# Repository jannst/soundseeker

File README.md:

# Soundseeker
The Soundseeker project originated from my need to measure the speed of sound traveling through wood, a crucial characteristic in selecting wood for musical instrument making. Regrettably, there was no affordable method available, prompting me to embark on building a device capable of measuring this parameter independently. The project commenced in 2017 with the development of the initial prototype. Throughout the process, I gained valuable insights, and I am currently at the third prototype stage, incorporating a custom PCB, surface-mount device (SMD) parts and even a step-up DC-DC converter to drive the piezo acuator.

This Repository contains only the source code for the third prototype.

## Prototype I (2017)
<div style="display: flex">

</div>
The first prototype used an ATMEAGA-8 as MCU and a Haribo sweets box as enclosure. 

## Prototype II (2020)

The second prototype uses a very powerful Teensy 4 board and utilises a display which even allows to visualise the waveform.

## Prototype III (2022)

The third prototype features custom PCBs and utilizes the RP2040 microcontroller, providing USB connectivity. The display was omitted to enable visualization of transmitted data through laptops or mobile phones connected via USB. The pre-amplifier for the piezo sensor is situated on the PCB to which the sensor is soldered, ensuring a very short, high-impedance signal path.

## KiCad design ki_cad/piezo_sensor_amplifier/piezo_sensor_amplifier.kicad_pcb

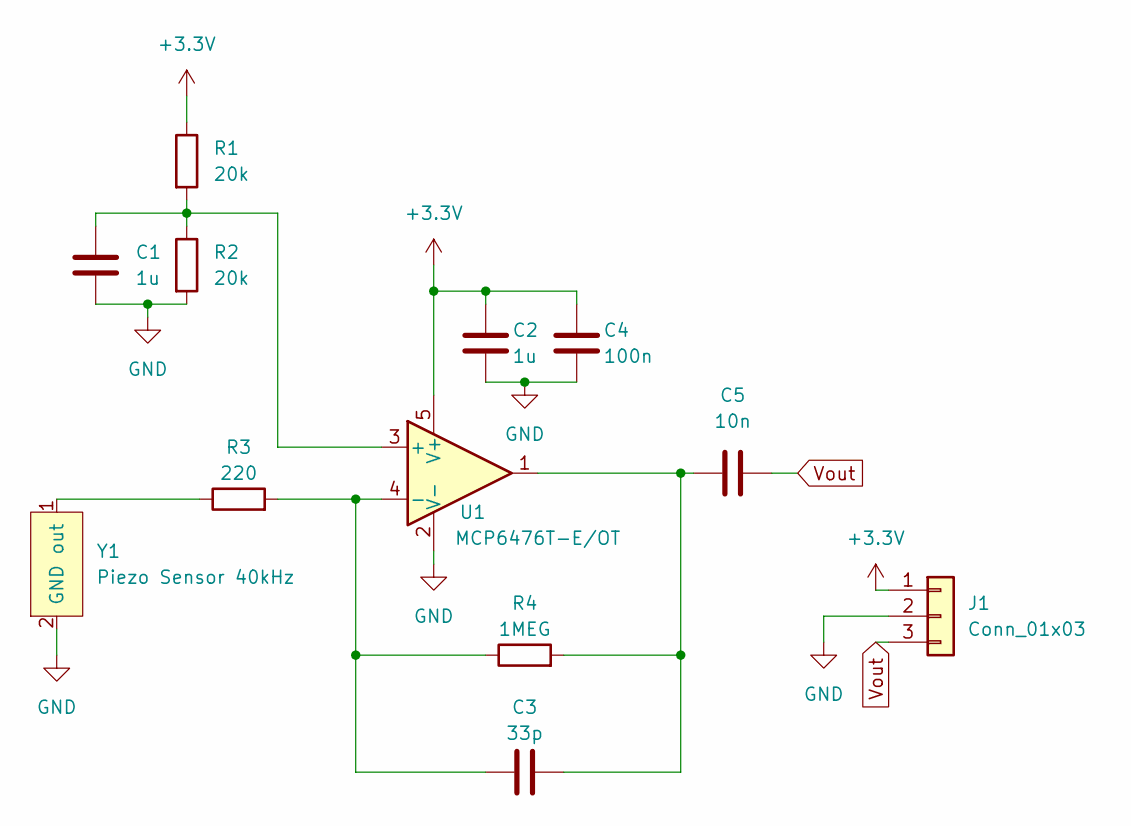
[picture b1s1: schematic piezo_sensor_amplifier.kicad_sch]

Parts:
C1, C2: 1u; R_0805_2012Metric_Pad1.20x1.40mm_HandSolder
C3: 33p; C_0805_2012Metric_Pad1.18x1.45mm_HandSolder
C4: 100n; C_0805_2012Metric_Pad1.18x1.45mm_HandSolder
C5: 10n; C_0805_2012Metric_Pad1.18x1.45mm_HandSolder
J1: Conn_01x03; PinHeader_1x03_P2.54mm_Vertical
R1, R2: 20k; R_0805_2012Metric_Pad1.20x1.40mm_HandSolder
R3: 220; R_0805_2012Metric_Pad1.20x1.40mm_HandSolder
R4: 1MEG; R_0805_2012Metric_Pad1.20x1.40mm_HandSolder
U1: MCP6476T-E/OT; SOT-23-5
Y1: Piezo Sensor 40kHz; piezo_sensor_D25mm

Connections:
+3.3V: C2.1, C4.1, J1.1, R1.1, U1.5 (V+)
GND: C1.2, C2.2, C4.2, J1.2, R2.2, U1.2 (V-), Y1.2 (GND)
unnamed: C1.1, R1.2, R2.1, U1.3 (+)
unnamed: C3.1, R3.2, R4.1, U1.4 (-)
unnamed: C3.2, C5.1, R4.2, U1.1
unnamed: R3.1, Y1.1 (out)
Vout: C5.2, J1.3

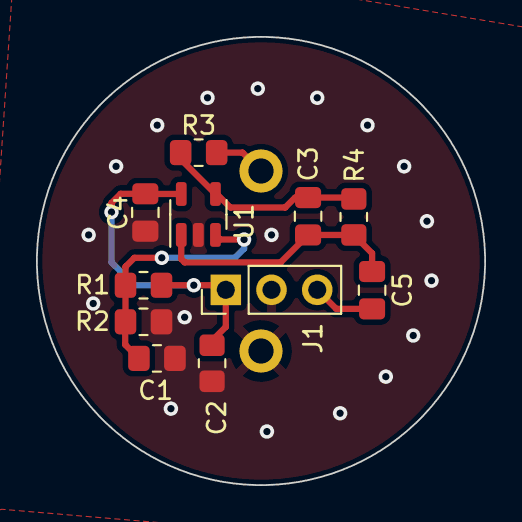
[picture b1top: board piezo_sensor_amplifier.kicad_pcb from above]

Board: 2 copper layers, 24.9 x 24.9 mm, 12 parts (0 on the bottom side), 7 nets.

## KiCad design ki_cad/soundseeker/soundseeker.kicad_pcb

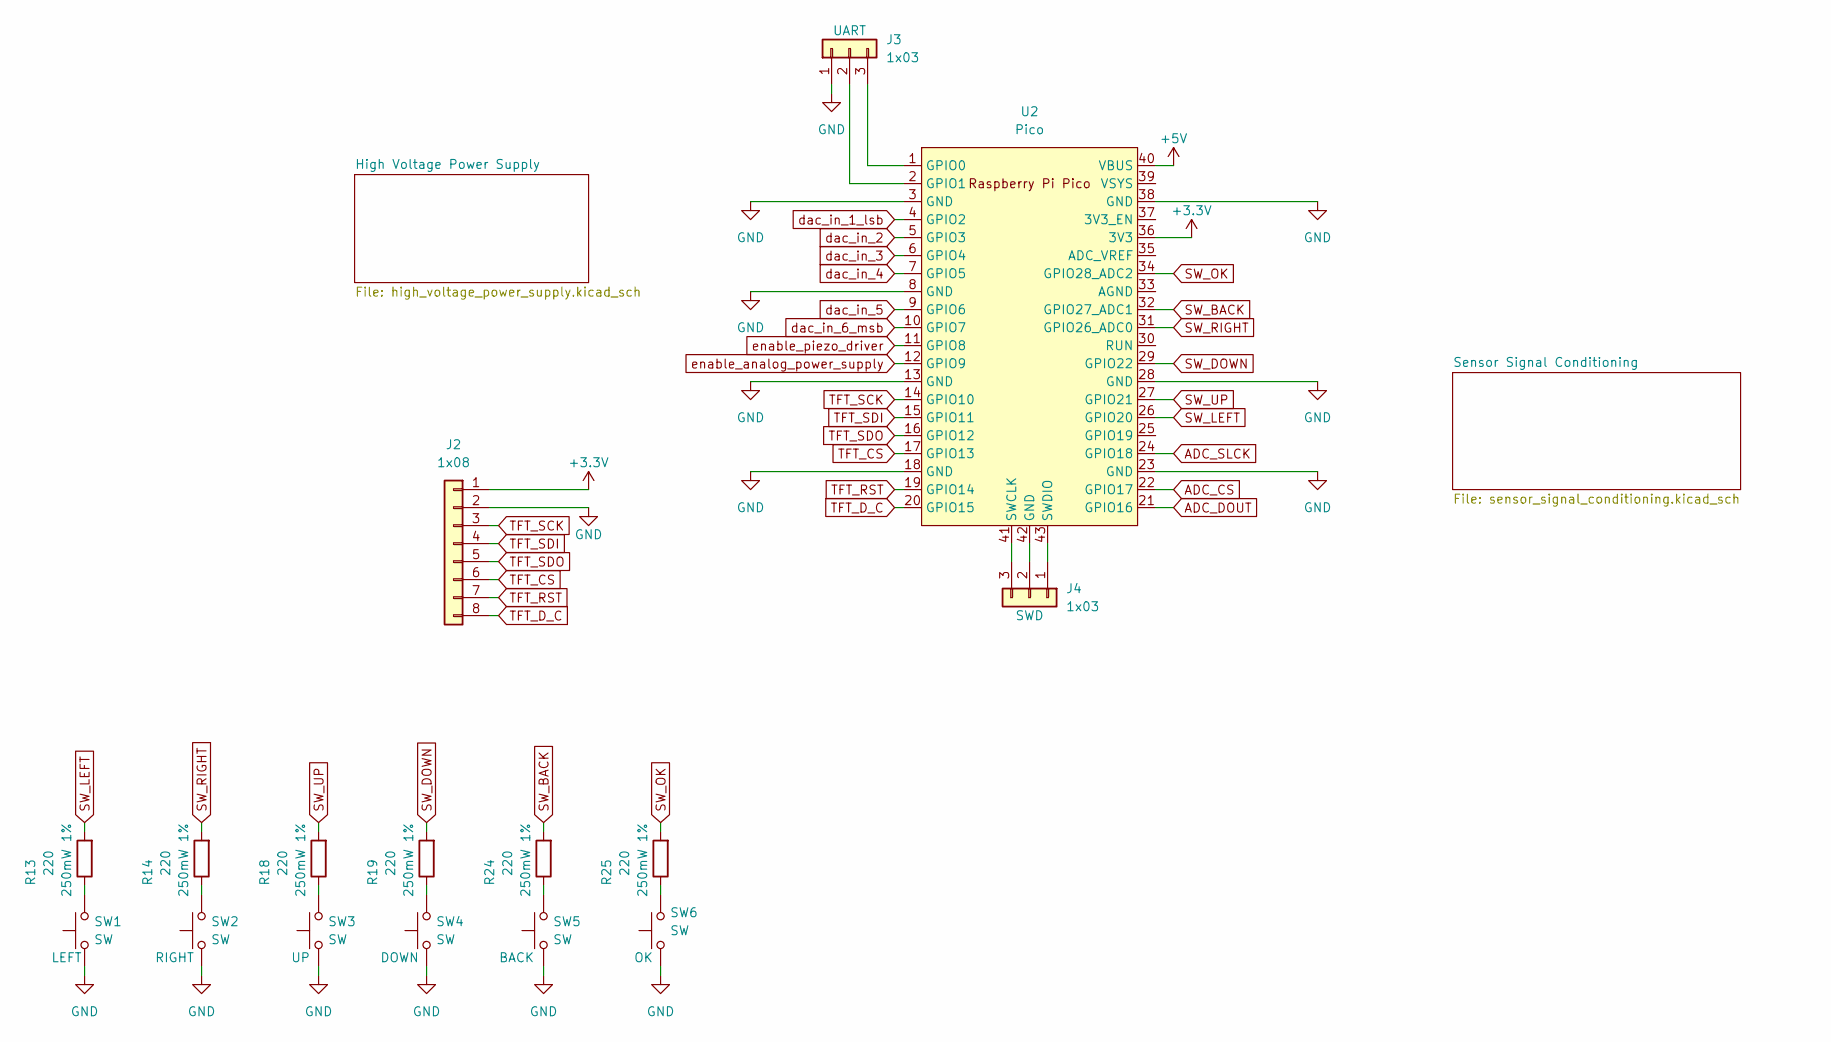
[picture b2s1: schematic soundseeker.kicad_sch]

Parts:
J2: 1x08; PinHeader_1x08_P2.54mm_Vertical
J3, J4: 1x03; PinHeader_1x03_P2.54mm_Vertical
R13, R14, R18, R19, R24, R25: 220; R_0805_2012Metric_Pad1.20x1.40mm_HandSolder
SW1, SW2, SW3, SW4, SW5, SW6: SW; SW_PUSH_6mm
U2: Pico; RPi_Pico_SMD_TH

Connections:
+3.3V: J2.1, U2.36 (3V3)
+5V: U2.40 (VBUS); also elsewhere on the board
ADC_CS: U2.22 (GPIO17); also elsewhere on the board
ADC_DOUT: U2.21 (GPIO16); also elsewhere on the board
ADC_SLCK: U2.24 (GPIO18); also elsewhere on the board
GND: J2.2, J3.1, SW1.1, SW2.1, SW3.1, SW4.1, SW5.1, SW6.1, U2.3 (GND), U2.8 (GND), U2.13 (GND), U2.18 (GND), U2.23 (GND), U2.28 (GND), U2.38 (GND); also elsewhere on the board
unnamed: J3.2, U2.2 (GPIO1)
unnamed: J3.3, U2.1 (GPIO0)
unnamed: J4.1, U2.43 (SWDIO)
unnamed: J4.2, U2.42 (GND)
unnamed: J4.3, U2.41 (SWCLK)
unnamed: R13.1, SW1.2
unnamed: R14.1, SW2.2
unnamed: R18.1, SW3.2
unnamed: R19.1, SW4.2
unnamed: R24.1, SW5.2
unnamed: R25.1, SW6.2
SW_BACK: R24.2, U2.32 (GPIO27_ADC1)
SW_DOWN: R19.2, U2.29 (GPIO22)
SW_LEFT: R13.2, U2.26 (GPIO20)
SW_OK: R25.2, U2.34 (GPIO28_ADC2)
SW_RIGHT: R14.2, U2.31 (GPIO26_ADC0)
SW_UP: R18.2, U2.27 (GPIO21)
TFT_CS: J2.6, U2.17 (GPIO13)
TFT_D_C: J2.8, U2.20 (GPIO15)
TFT_RST: J2.7, U2.19 (GPIO14)
TFT_SCK: J2.3, U2.14 (GPIO10)
TFT_SDI: J2.4, U2.15 (GPIO11)
TFT_SDO: J2.5, U2.16 (GPIO12)
dac_in_1_lsb: U2.4 (GPIO2); also elsewhere on the board
dac_in_2: U2.5 (GPIO3); also elsewhere on the board
dac_in_3: U2.6 (GPIO4); also elsewhere on the board
dac_in_4: U2.7 (GPIO5); also elsewhere on the board
dac_in_5: U2.9 (GPIO6); also elsewhere on the board
dac_in_6_msb: U2.10 (GPIO7); also elsewhere on the board
enable_analog_power_supply: U2.12 (GPIO9); also elsewhere on the board
enable_piezo_driver: U2.11 (GPIO8); also elsewhere on the board

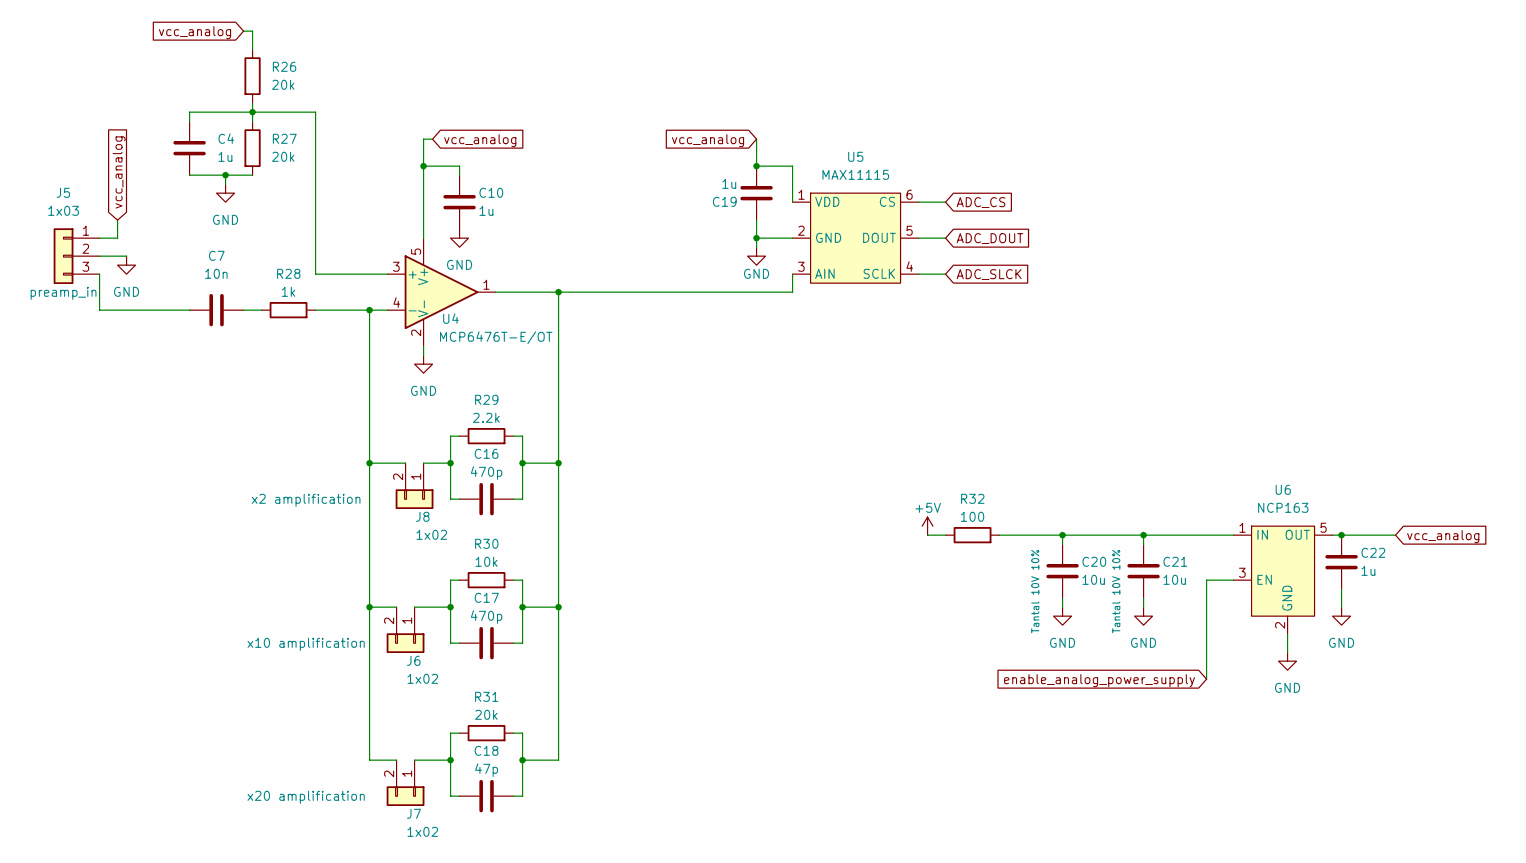
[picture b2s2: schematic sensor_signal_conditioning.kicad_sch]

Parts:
C4, C10, C19, C22: 1u; C_0805_2012Metric_Pad1.18x1.45mm_HandSolder
C7: 10n; C_0805_2012Metric_Pad1.18x1.45mm_HandSolder
C16, C17: 470p; C_0805_2012Metric_Pad1.18x1.45mm_HandSolder
C18: 47p; C_0805_2012Metric_Pad1.18x1.45mm_HandSolder
C20, C21: 10u; C_1206_3216Metric_Pad1.33x1.80mm_HandSolder
J5: 1x03; PinHeader_1x03_P2.54mm_Vertical
J6, J7, J8: 1x02; PinHeader_1x02_P2.54mm_Vertical
R26, R27, R31: 20k; R_0805_2012Metric_Pad1.20x1.40mm_HandSolder
R28: 1k; R_0805_2012Metric_Pad1.20x1.40mm_HandSolder
R29: 2.2k; R_0805_2012Metric_Pad1.20x1.40mm_HandSolder
R30: 10k; R_0805_2012Metric_Pad1.20x1.40mm_HandSolder
R32: 100; R_0805_2012Metric_Pad1.20x1.40mm_HandSolder
U4: MCP6476T-E/OT; SOT-23-5
U5: MAX11115; SOT-23-6_Handsoldering
U6: NCP163; SOT-23-5_HandSoldering

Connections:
+5V: R32.1; also elsewhere on the board
ADC_CS: U5.6 (CS); also elsewhere on the board
ADC_DOUT: U5.5 (DOUT); also elsewhere on the board
ADC_SLCK: U5.4 (SCLK); also elsewhere on the board
GND: C4.2, C10.2, C19.1, C20.2, C21.2, C22.2, J5.2, R27.2, U4.2 (V-), U5.2 (GND), U6.2 (GND); also elsewhere on the board
unnamed: C4.1, R26.2, R27.1, U4.3 (+)
unnamed: C7.1, J5.3
unnamed: C7.2, R28.1
unnamed: C16.1, J8.1, R29.1
unnamed: C16.2, C17.2, C18.2, R29.2, R30.2, R31.2, U4.1, U5.3 (AIN)
unnamed: C17.1, J6.1, R30.1
unnamed: C18.1, J7.1, R31.1
unnamed: C20.1, C21.1, R32.2, U6.1 (IN)
unnamed: J6.2, J7.2, J8.2, R28.2, U4.4 (-)
enable_analog_power_supply: U6.3 (EN); also elsewhere on the board
vcc_analog: C10.1, C19.2, C22.1, J5.1, R26.1, U4.5 (V+), U5.1 (VDD), U6.5 (OUT)

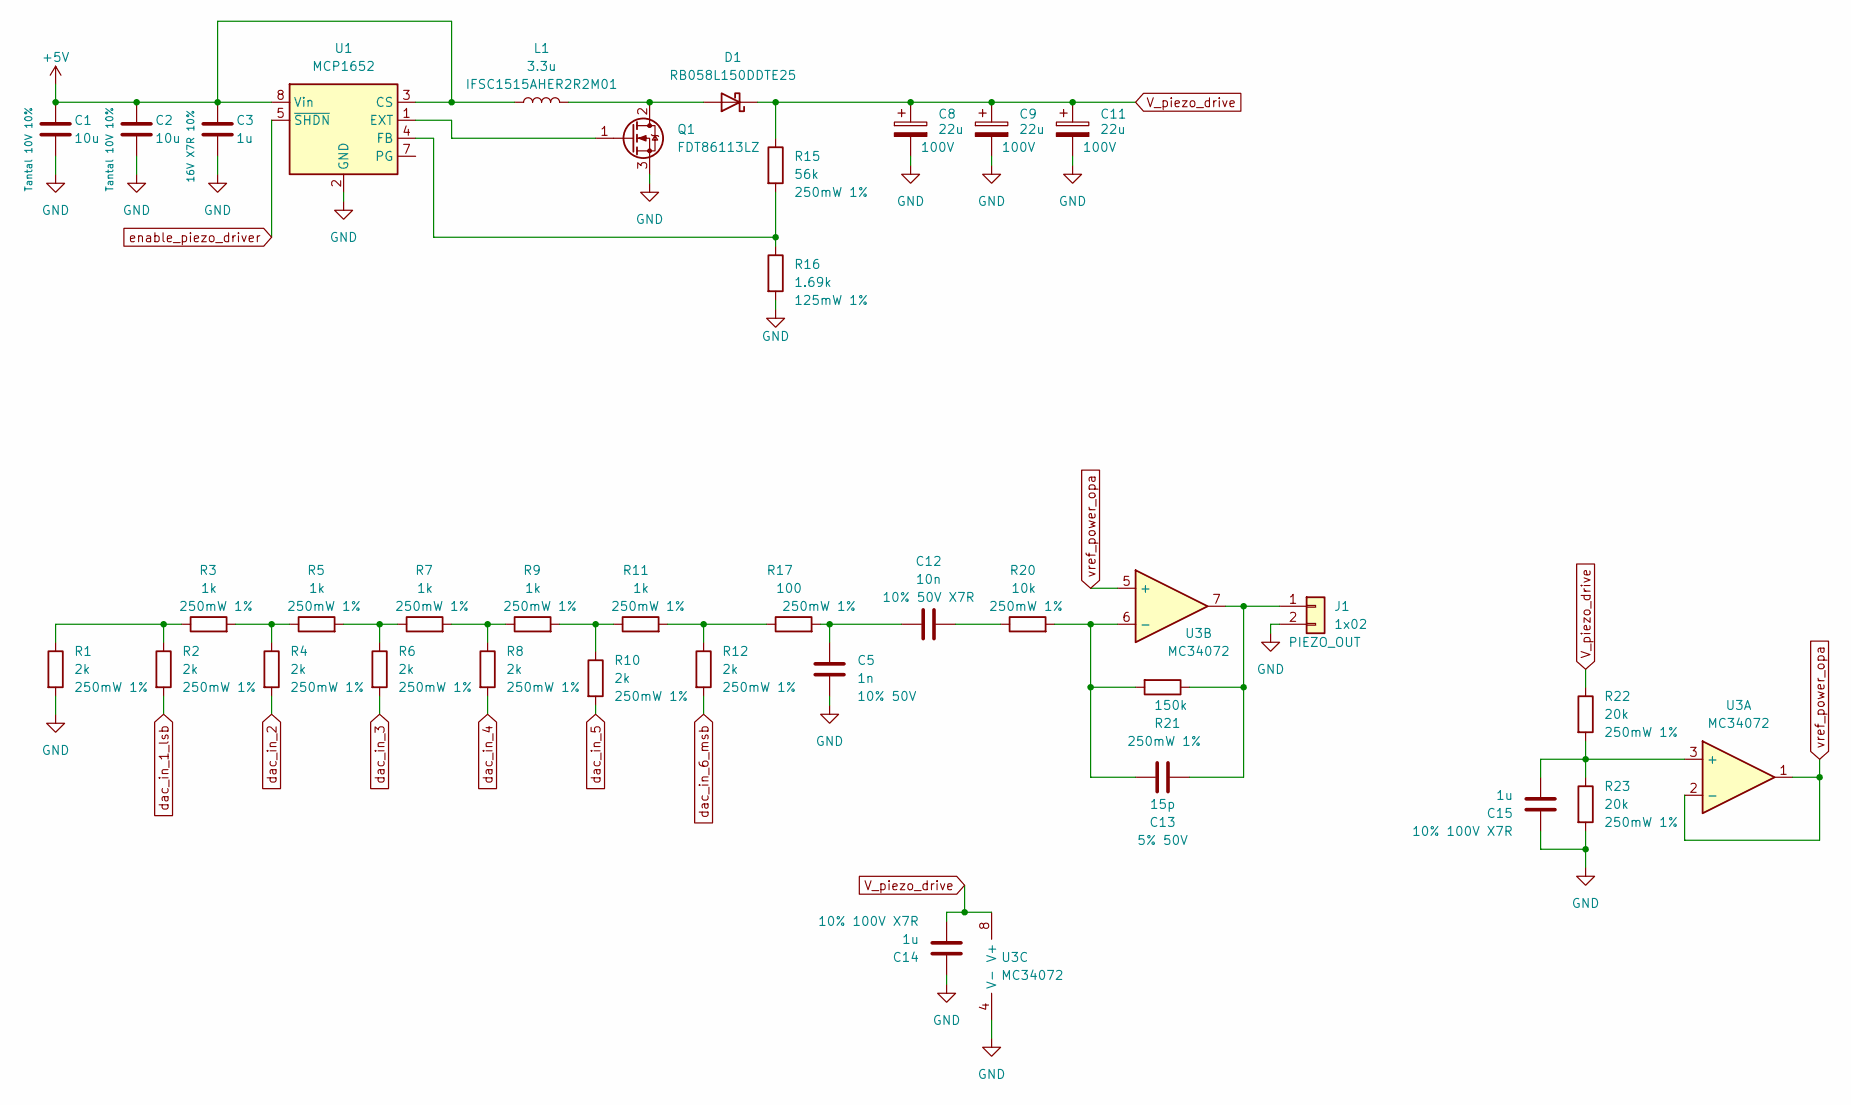
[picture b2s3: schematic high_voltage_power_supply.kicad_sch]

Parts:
C1, C2: 10u; C_1206_3216Metric_Pad1.33x1.80mm_HandSolder
C3: 1u; C_0805_2012Metric_Pad1.18x1.45mm_HandSolder
C5: 1n; C_0805_2012Metric_Pad1.18x1.45mm_HandSolder
C8, C9, C11: 22u; CP_Elec_8x10.5
C12: 10n; C_0805_2012Metric_Pad1.18x1.45mm_HandSolder
C13: 15p; C_0805_2012Metric_Pad1.18x1.45mm_HandSolder
C14, C15: 1u; C_1206_3216Metric_Pad1.33x1.80mm_HandSolder
D1: RB058L150DDTE25; D_SMA
J1: 1x02; PinHeader_1x02_P2.54mm_Vertical
L1: 3.3u; L_Vishay_IFSC-1515AH_4x4x1.8mm
Q1: FDT86113LZ; SOT-223-3_TabPin2
R1, R2, R4, R6, R8, R10, R12: 2k; R_0805_2012Metric_Pad1.20x1.40mm_HandSolder
R3, R5, R7, R9, R11: 1k; R_0805_2012Metric_Pad1.20x1.40mm_HandSolder
R15: 56k; R_0805_2012Metric_Pad1.20x1.40mm_HandSolder
R16: 1.69k; R_0805_2012Metric_Pad1.20x1.40mm_HandSolder
R17: 100; R_0805_2012Metric_Pad1.20x1.40mm_HandSolder
R20: 10k; R_0805_2012Metric_Pad1.20x1.40mm_HandSolder
R21: 150k; R_0805_2012Metric_Pad1.20x1.40mm_HandSolder
R22, R23: 20k; R_0805_2012Metric_Pad1.20x1.40mm_HandSolder
U1: MCP1652; MSOP-8_3x3mm_P0.65mm
U3: MC34072; SOIC-8_3.9x4.9mm_P1.27mm

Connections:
+5V: C1.1, C2.1, C3.1, L1.1, U1.3 (CS), U1.8 (Vin); also elsewhere on the board
GND: C1.2, C2.2, C3.2, C5.2, C8.2, C9.2, C11.2, C14.1, C15.1, J1.2, Q1.3 (S), R1.2, R16.2, R23.2, U1.2 (GND), U3.4 (V-); also elsewhere on the board
unnamed: C5.1, C12.1, R17.2
unnamed: C12.2, R20.1
unnamed: C13.1, J1.1, R21.1, U3.7
unnamed: C13.2, R20.2, R21.2, U3.6 (-)
unnamed: C15.2, R22.2, R23.1, U3.3 (+)
unnamed: D1.2 (A), L1.2, Q1.2 (D)
unnamed: Q1.1 (G), U1.1 (EXT)
unnamed: R1.1, R2.1, R3.1
unnamed: R3.2, R4.1, R5.1
unnamed: R5.2, R6.1, R7.1
unnamed: R7.2, R8.1, R9.1
unnamed: R9.2, R10.1, R11.1
unnamed: R11.2, R12.1, R17.1
unnamed: R15.2, R16.1, U1.4 (FB)
V_piezo_drive: C8.1, C9.1, C11.1, C14.2, D1.1 (K), R15.1, R22.1, U3.8 (V+)
dac_in_1_lsb: R2.2; also elsewhere on the board
dac_in_2: R4.2; also elsewhere on the board
dac_in_3: R6.2; also elsewhere on the board
dac_in_4: R8.2; also elsewhere on the board
dac_in_5: R10.2; also elsewhere on the board
dac_in_6_msb: R12.2; also elsewhere on the board
enable_piezo_driver: U1.5 (~SHDN); also elsewhere on the board
vref_power_opa: U3.1, U3.2 (-), U3.5 (+)

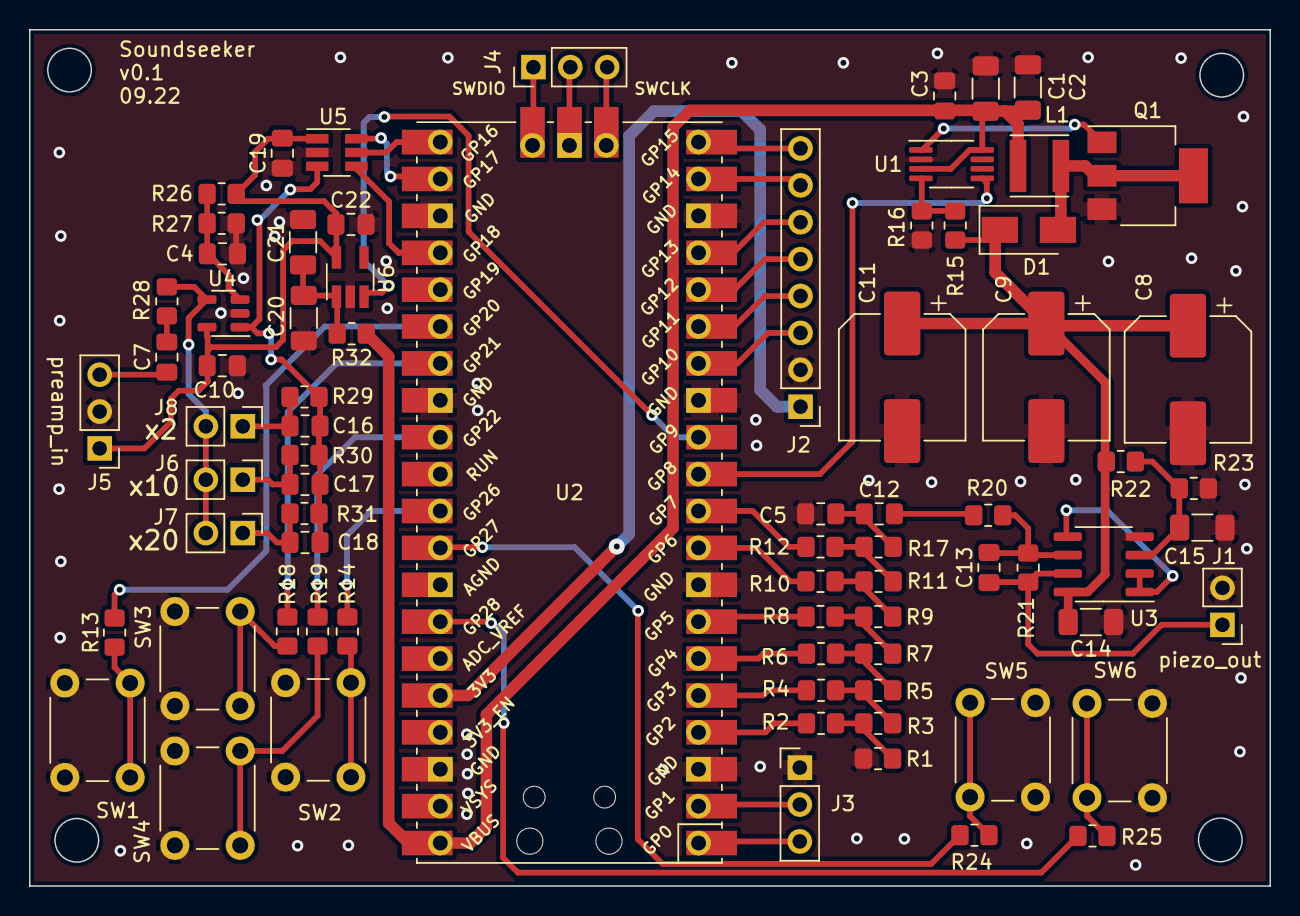
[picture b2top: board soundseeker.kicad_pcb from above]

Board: 2 copper layers, 85.4 x 59.0 mm, 76 parts (0 on the bottom side), 63 nets.

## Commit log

2021-06-14 initial workspace export/begin docs
2021-06-14 typo
2021-06-14 text verbesserungen docs
2021-06-20 add gallery
2021-06-20 add pics for first prototype
2022-09-13 add kicad
2022-09-13 initial firmware commit
2022-09-13 first build running
2022-09-14 cleanup firmware code
2022-09-14 first working pwm sine generator
2022-09-15 clean pwm code
2022-09-15 add first attempt of parallel r2r-ladder driver
2022-09-16 20-50kHz sweep working
2022-09-16 proof if concept signal generator :)
2022-09-17 schematic
2022-09-17 add boost converter calculator
2022-09-27 add preamp schematic
2022-10-01 add buttons and display spi connections
2022-10-02 sounseeker base board (evaluartion) PCB layout
2022-10-03 finish base board (evaluation)
2022-11-02 first working hardware board :)
2022-11-04 first working demo of SPI ADC sampling
2022-11-06 WIP first testing sessions
2023-11-26 add readme
